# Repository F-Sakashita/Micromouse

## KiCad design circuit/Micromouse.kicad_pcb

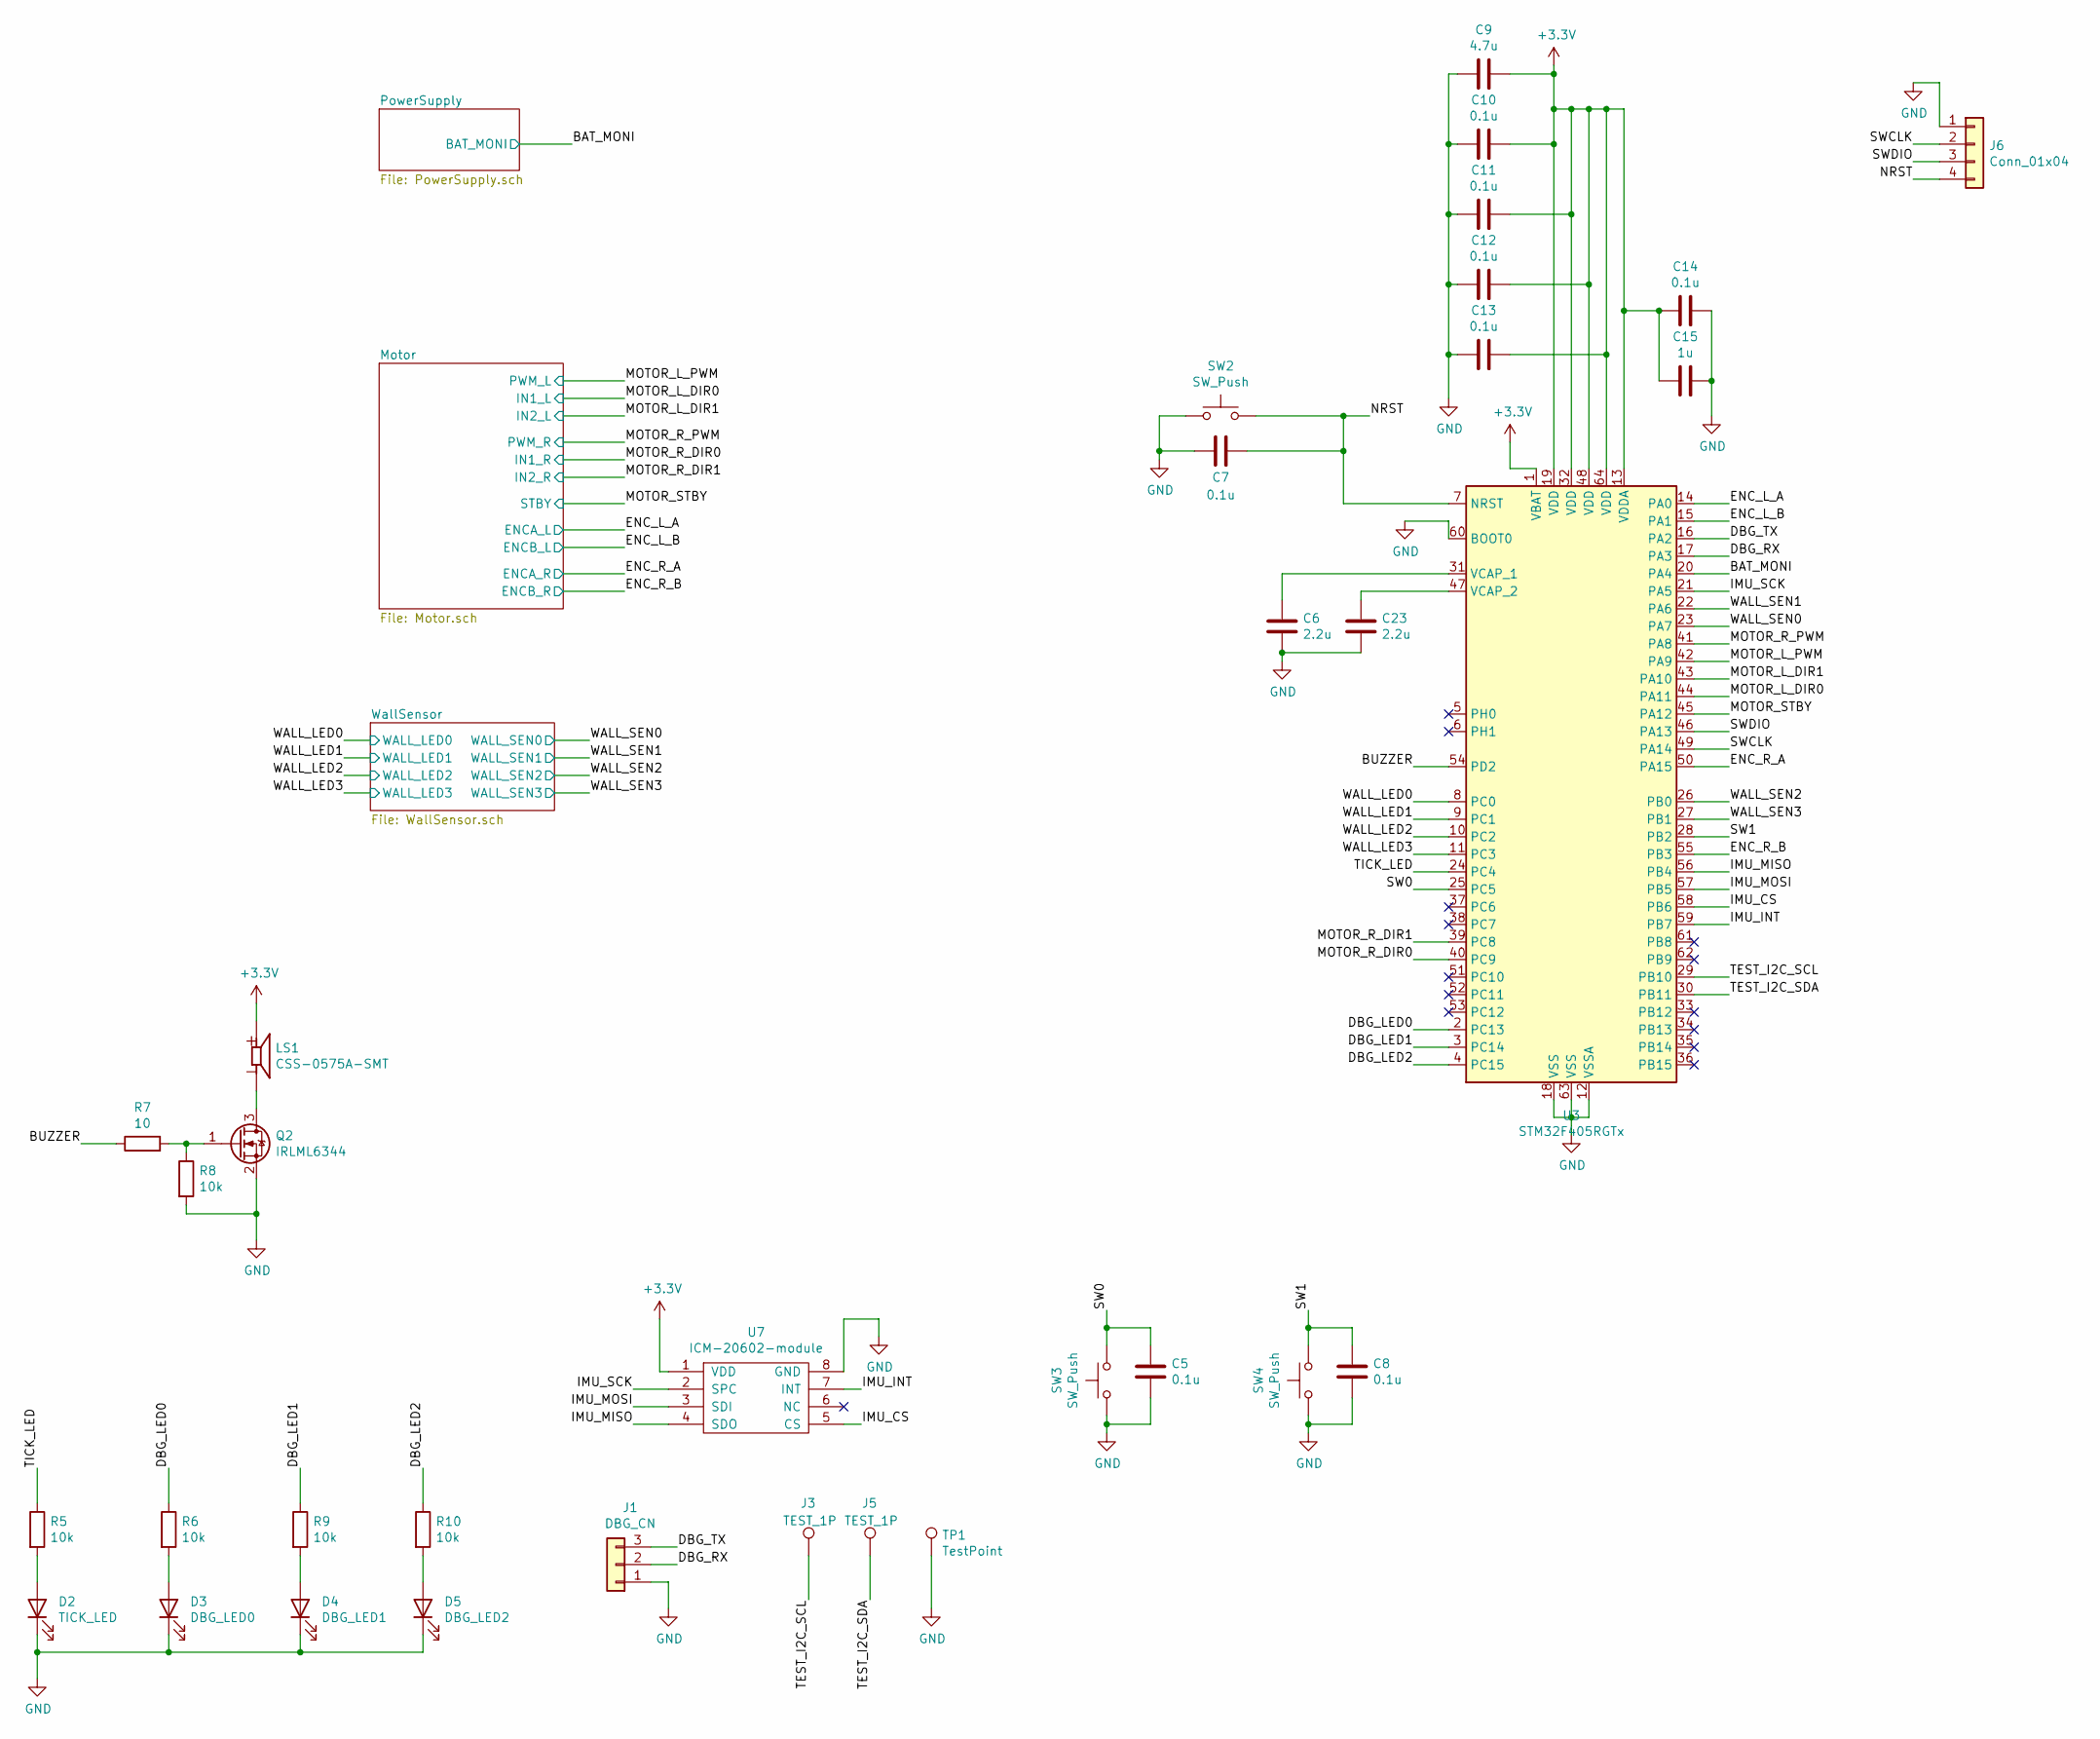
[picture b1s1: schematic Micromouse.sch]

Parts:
C5, C7, C8, C10, C11, C12, C13, C14: 0.1u; C_0603_1608Metric
C6, C23: 2.2u; C_0603_1608Metric
C9: 4.7u; C_0603_1608Metric
C15: 1u; C_0603_1608Metric
D2: TICK_LED; LED_0603_1608Metric
D3: DBG_LED0; LED_0603_1608Metric
D4: DBG_LED1; LED_0603_1608Metric
D5: DBG_LED2; LED_0603_1608Metric
J1: DBG_CN; PinSocket_1x03_P2.54mm_Vertical
J3, J5: TEST_1P; TestPoint_Pad_D1.0mm
J6: Conn_01x04; PinSocket_1x04_P2.54mm_Vertical
LS1: CSS-0575A-SMT; CUI_CSS-0575A-SMT
Q2: IRLML6344; SOT-23
R5, R6, R8, R9, R10: 10k; R_0603_1608Metric
R7: 10; R_0603_1608Metric
SW2, SW3, SW4: SW_Push; SW_TACT_ALPS_SKRPABE010
TP1: TestPoint; TestPoint_Pad_D1.0mm
U3: STM32F405RGTx; LQFP-64_10x10mm_P0.5mm
U7: ICM-20602-module; ICM-20602

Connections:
+3V3: C9.1, C10.1, C11.1, C12.1, C13.1, C14.2, C15.2, LS1.1, U3.1 (VBAT), U3.13 (VDDA), U3.19 (VDD), U3.32 (VDD), U3.48 (VDD), U3.64 (VDD), U7.1 (VDD); also elsewhere on the board
/BAT_MONI: U3.20 (PA4); also elsewhere on the board
/BUZZER: R7.1, U3.54 (PD2)
/DBG_LED0: R6.1, U3.2 (PC13)
/DBG_LED1: R9.1, U3.3 (PC14)
/DBG_LED2: R10.1, U3.4 (PC15)
/DBG_RX: J1.2, U3.17 (PA3)
/DBG_TX: J1.3, U3.16 (PA2)
/ENC_L_A: U3.14 (PA0); also elsewhere on the board
/ENC_L_B: U3.15 (PA1); also elsewhere on the board
/ENC_R_A: U3.50 (PA15); also elsewhere on the board
/ENC_R_B: U3.55 (PB3); also elsewhere on the board
/IMU_CS: U3.58 (PB6), U7.5 (CS)
/IMU_INT: U3.59 (PB7), U7.7 (INT)
/IMU_MISO: U3.56 (PB4), U7.4 (SDO)
/IMU_MOSI: U3.57 (PB5), U7.3 (SDI)
/IMU_SCK: U3.21 (PA5), U7.2 (SPC)
/MOTOR_L_DIR0: U3.44 (PA11); also elsewhere on the board
/MOTOR_L_DIR1: U3.43 (PA10); also elsewhere on the board
/MOTOR_L_PWM: U3.42 (PA9); also elsewhere on the board
/MOTOR_R_DIR0: U3.40 (PC9); also elsewhere on the board
/MOTOR_R_DIR1: U3.39 (PC8); also elsewhere on the board
/MOTOR_R_PWM: U3.41 (PA8); also elsewhere on the board
/MOTOR_STBY: U3.45 (PA12); also elsewhere on the board
/NRST: C7.1, J6.4, SW2.2, U3.7 (NRST)
/SW0: C5.1, SW3.2, U3.25 (PC5)
/SW1: C8.1, SW4.2, U3.28 (PB2)
/SWCLK: J6.2, U3.49 (PA14)
/SWDIO: J6.3, U3.46 (PA13)
/TEST_I2C_SCL: J3.1, U3.29 (PB10)
/TEST_I2C_SDA: J5.1, U3.30 (PB11)
/TICK_LED: R5.1, U3.24 (PC4)
/WALL_LED0: U3.8 (PC0); also elsewhere on the board
/WALL_LED1: U3.9 (PC1); also elsewhere on the board
/WALL_LED2: U3.10 (PC2); also elsewhere on the board
/WALL_LED3: U3.11 (PC3); also elsewhere on the board
/WALL_SEN0: U3.23 (PA7); also elsewhere on the board
/WALL_SEN1: U3.22 (PA6); also elsewhere on the board
/WALL_SEN2: U3.26 (PB0); also elsewhere on the board
/WALL_SEN3: U3.27 (PB1); also elsewhere on the board
GND: C5.2, C6.2, C7.2, C8.2, C9.2, C10.2, C11.2, C12.2, C13.2, C14.1, C15.1, C23.2, D2.1 (K), D3.1 (K), D4.1 (K), D5.1 (K), J1.1, J6.1, Q2.2 (S), R8.2, SW2.1, SW3.1, SW4.1, TP1.1, U3.12 (VSSA), U3.18 (VSS), U3.60 (BOOT0), U3.63 (VSS), U7.8 (GND); also elsewhere on the board
unnamed: C6.1, U3.31 (VCAP_1)
unnamed: C23.1, U3.47 (VCAP_2)
unnamed: D2.2 (A), R5.2
unnamed: D3.2 (A), R6.2
unnamed: D4.2 (A), R9.2
unnamed: D5.2 (A), R10.2
unnamed: LS1.2, Q2.3 (D)
unnamed: Q2.1 (G), R7.2, R8.1

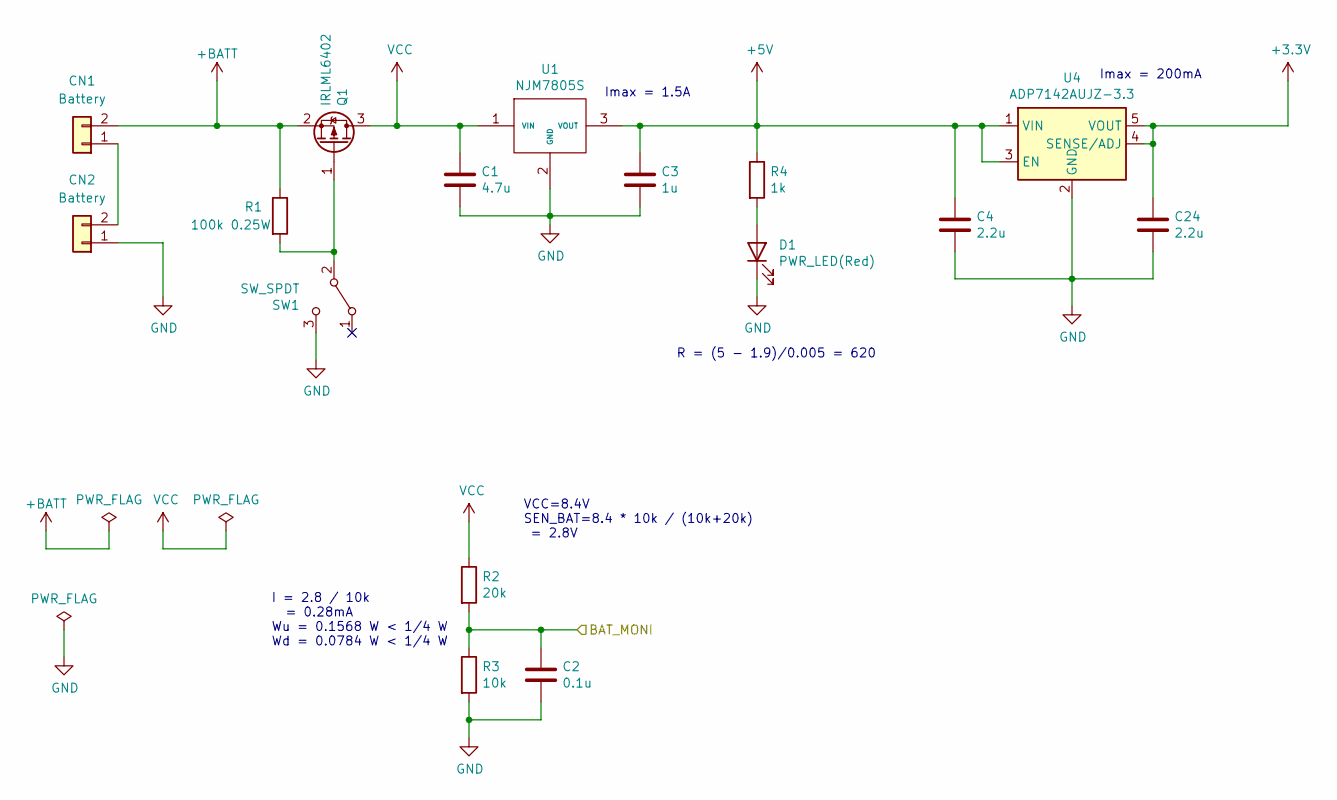
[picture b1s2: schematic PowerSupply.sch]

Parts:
C1: 4.7u; C_0805_2012Metric
C2: 0.1u; C_0603_1608Metric
C3: 1u; C_0603_1608Metric
C4, C24: 2.2u; C_0603_1608Metric
CN1, CN2: Battery; JST_PH_B2B-PH-K_1x02_P2.00mm_Vertical
D1: PWR_LED(Red); LED_0603_1608Metric
Q1: IRLML6402; SOT-23
R1: 100k 0.25W; R_0603_1608Metric
R2: 20k; R_0805_2012Metric
R3: 10k; R_0805_2012Metric
R4: 1k; R_0603_1608Metric
SW1: SW_SPDT; SW_CuK_JS202011CQN_DPDT_Straight
U1: NJM7805S; TO-252-2
U4: ADP7142AUJZ-3.3; TSOT-23-5

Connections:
+3V3: C24.1, U4.4 (SENSE/ADJ), U4.5 (VOUT); also elsewhere on the board
+5V: C3.1, C4.1, R4.1, U1.3 (VOUT), U4.1 (VIN), U4.3 (EN); also elsewhere on the board
+BATT: CN1.2, Q1.2 (S), R1.1
/BAT_MONI: C2.1, R2.2, R3.1; also elsewhere on the board
GND: C1.2, C2.2, C3.2, C4.2, C24.2, CN2.1, D1.1 (K), R3.2, SW1.3 (C), U1.2 (GND), U4.2 (GND); also elsewhere on the board
unnamed: CN1.1, CN2.2
unnamed: D1.2 (A), R4.2
unnamed 64: Q1.1 (G), R1.2, SW1.2 (B); also elsewhere on the board
VCC: C1.1, Q1.3 (D), R2.1, U1.1 (VIN); also elsewhere on the board

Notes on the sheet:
VCC=8.4V SEN_BAT=8.4 * 10k / (10k+20k) = 2.8V
Imax = 1.5A
Imax = 200mA
R = (5 - 1.9)/0.005 = 620
I = 2.8 / 10k = 0.28mA Wu = 0.1568 W < 1/4 W Wd = 0.0784 W < 1/4 W

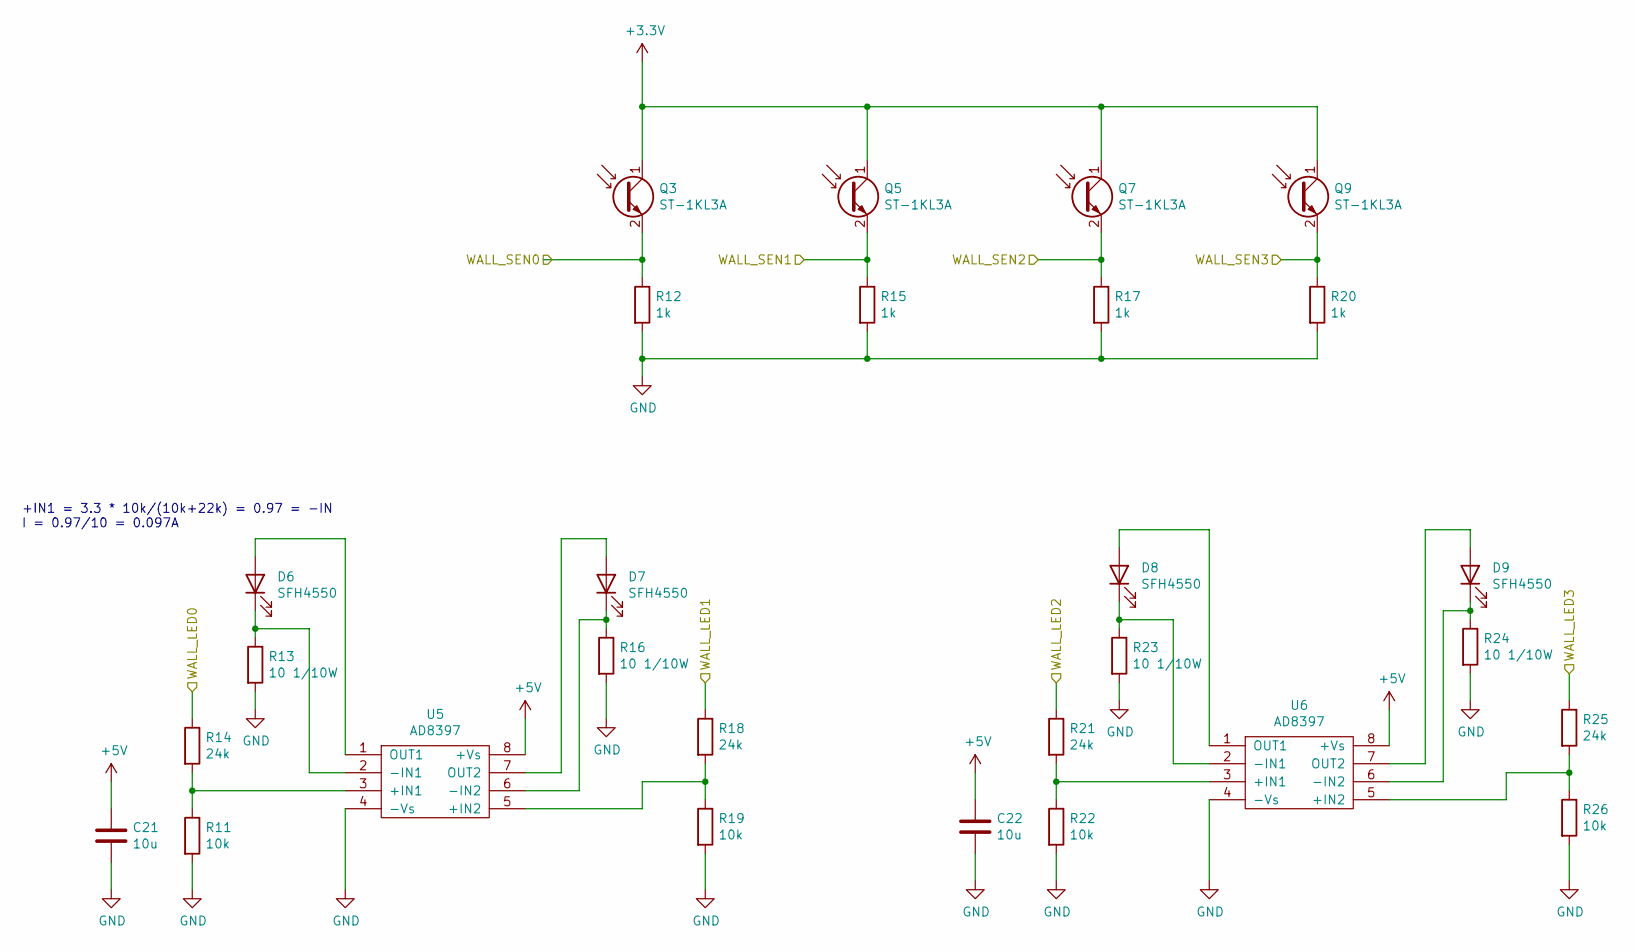
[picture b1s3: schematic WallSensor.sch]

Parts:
C21, C22: 10u; C_0603_1608Metric
D6, D7: SFH4550; LED_D5.0mm_Horizontal_O3.81mm_Z9.0mm
D8, D9: SFH4550; LED_D5.0mm_Horizontal_O3.81mm_Z9.0mm_reverse
Q3, Q5, Q7, Q9: ST-1KL3A; ST-1KL3A_ForWall
R11, R19, R22, R26: 10k; R_0603_1608Metric
R12, R15, R17, R20: 1k; R_0603_1608Metric
R13, R16, R23, R24: 10 1/10W; R_0603_1608Metric
R14, R18, R21, R25: 24k; R_0603_1608Metric
U5, U6: AD8397; SOIC-8_3.9x4.9mm_P1.27mm

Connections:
+3V3: Q3.1 (C), Q5.1 (C), Q7.1 (C), Q9.1 (C); also elsewhere on the board
+5V: C21.1, C22.1, U5.8 (+Vs), U6.8 (+Vs); also elsewhere on the board
/WALL_LED0: R14.1; also elsewhere on the board
/WALL_LED1: R18.1; also elsewhere on the board
/WALL_LED2: R21.1; also elsewhere on the board
/WALL_LED3: R25.1; also elsewhere on the board
/WALL_SEN0: Q3.2 (E), R12.1; also elsewhere on the board
/WALL_SEN1: Q5.2 (E), R15.1; also elsewhere on the board
/WALL_SEN2: Q7.2 (E), R17.1; also elsewhere on the board
/WALL_SEN3: Q9.2 (E), R20.1; also elsewhere on the board
GND: C21.2, C22.2, R11.2, R12.2, R13.2, R15.2, R16.2, R17.2, R19.2, R20.2, R22.2, R23.2, R24.2, R26.2, U5.4 (-Vs), U6.4 (-Vs); also elsewhere on the board
unnamed: D6.1 (K), R13.1, U5.2 (-IN1)
unnamed: D6.2 (A), U5.1 (OUT1)
unnamed: D7.1 (K), R16.1, U5.6 (-IN2)
unnamed: D7.2 (A), U5.7 (OUT2)
unnamed: D8.1 (K), R23.1, U6.2 (-IN1)
unnamed: D8.2 (A), U6.1 (OUT1)
unnamed: D9.1 (K), R24.1, U6.6 (-IN2)
unnamed: D9.2 (A), U6.7 (OUT2)
unnamed: R11.1, R14.2, U5.3 (+IN1)
unnamed: R18.2, R19.1, U5.5 (+IN2)
unnamed: R21.2, R22.1, U6.3 (+IN1)
unnamed: R25.2, R26.1, U6.5 (+IN2)

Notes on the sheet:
+IN1 = 3.3 * 10k/(10k+22k) = 0.97 = -IN I = 0.97/10 = 0.097A

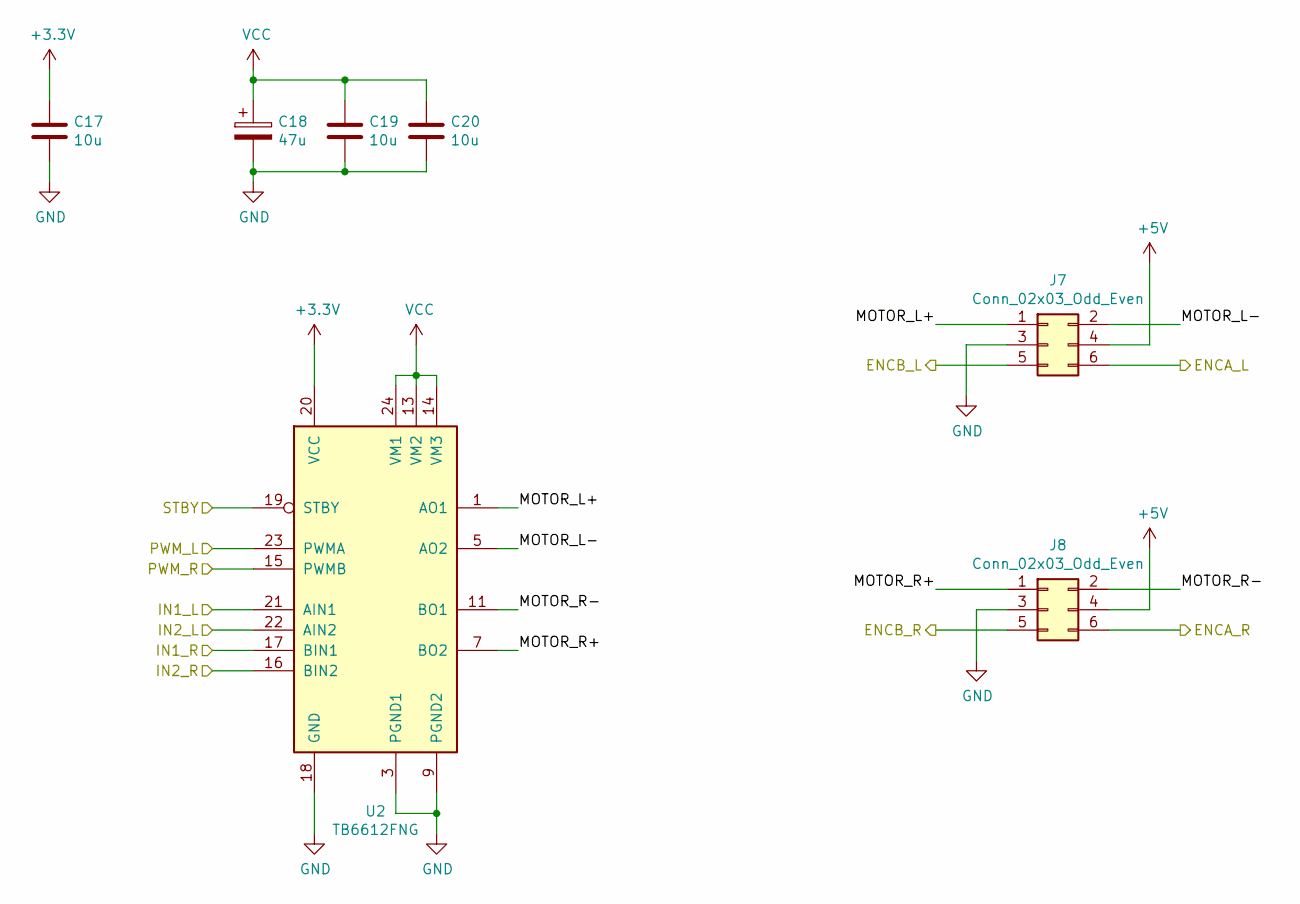
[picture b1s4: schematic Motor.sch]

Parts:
C17, C19, C20: 10u; C_0805_2012Metric
C18: 47u; CP_Elec_6.3x7.7
J7, J8: Conn_02x03_Odd_Even; IDC-Header_2x03_P2.54mm_Vertical
U2: TB6612FNG; SSOP-24_5.3x8.2mm_P0.65mm

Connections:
+3V3: C17.1, U2.20 (VCC); also elsewhere on the board
+5V: J7.4, J8.4; also elsewhere on the board
/ENC_L_A: J7.6; also elsewhere on the board
/ENC_L_B: J7.5; also elsewhere on the board
/ENC_R_A: J8.6; also elsewhere on the board
/ENC_R_B: J8.5; also elsewhere on the board
/MOTOR_L_DIR0: U2.21 (AIN1); also elsewhere on the board
/MOTOR_L_DIR1: U2.22 (AIN2); also elsewhere on the board
/MOTOR_L_PWM: U2.23 (PWMA); also elsewhere on the board
/MOTOR_R_DIR0: U2.17 (BIN1); also elsewhere on the board
/MOTOR_R_DIR1: U2.16 (BIN2); also elsewhere on the board
/MOTOR_R_PWM: U2.15 (PWMB); also elsewhere on the board
/MOTOR_STBY: U2.19 (STBY); also elsewhere on the board
/Motor/MOTOR_L+: J7.1, U2.1 (AO1), U2.2 (AO1)
/Motor/MOTOR_L-: J7.2, U2.5 (AO2), U2.6 (AO2)
/Motor/MOTOR_R+: J8.1, U2.7 (BO2), U2.8 (BO2)
/Motor/MOTOR_R-: J8.2, U2.11 (BO1), U2.12 (BO1)
GND: C17.2, C18.2, C19.2, C20.2, J7.3, J8.3, U2.3 (PGND1), U2.4 (PGND1), U2.9 (PGND2), U2.10 (PGND2), U2.18 (GND); also elsewhere on the board
VCC: C18.1, C19.1, C20.1, U2.13 (VM2), U2.14 (VM3), U2.24 (VM1); also elsewhere on the board

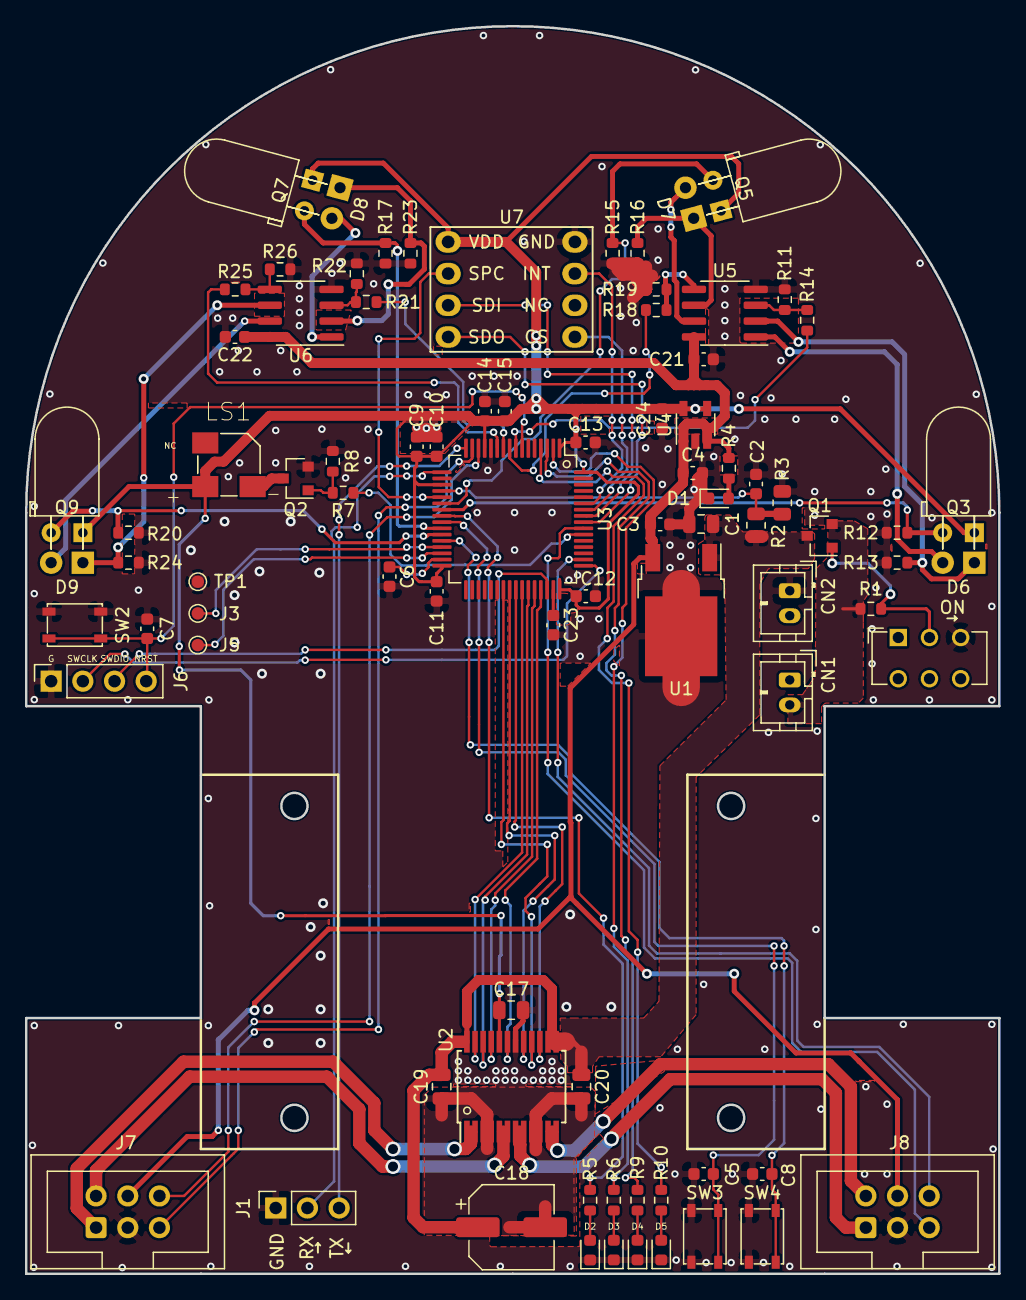
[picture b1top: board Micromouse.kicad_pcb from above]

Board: 2 copper layers, 78.0 x 100.0 mm, 85 parts (0 on the bottom side), 71 nets.

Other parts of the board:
ON: SW_SPDT; SW_CuK_JS202011CQN_DPDT_Straight

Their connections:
GND: ON.3; also elsewhere on the board
unnamed 64: ON.2; also elsewhere on the board

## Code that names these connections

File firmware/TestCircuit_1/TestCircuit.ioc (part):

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Mcu.Name=STM32F405RGTx
Mcu.Package=LQFP64
Mcu.UserName=STM32F405RGTx
PA0-WKUP.GPIOParameters=GPIO_Label
PA0-WKUP.GPIO_Label=ENC_R_A
PA0-WKUP.Signal=S_TIM5_CH1
PA1.GPIOParameters=GPIO_Label
PA1.GPIO_Label=ENC_R_B
PA1.Signal=S_TIM5_CH2
PA10.GPIOParameters=GPIO_Label
PA10.GPIO_Label=MOTOR_L_DIR1
PA10.Signal=GPIO_Output
PA11.GPIOParameters=GPIO_Label
PA11.GPIO_Label=MOTOR_L_DIR0
PA11.Signal=GPIO_Output
PA12.GPIOParameters=GPIO_Label
PA12.GPIO_Label=MOTOR_STBY
PA12.Signal=GPIO_Output
PA13.Mode=Serial_Wire
PA13.Signal=SYS_JTMS-SWDIO
PA14.Mode=Serial_Wire
PA14.Signal=SYS_JTCK-SWCLK
PA15.GPIOParameters=GPIO_Label
PA15.GPIO_Label=ENC_L_A
PA15.Signal=S_TIM2_CH1_ETR
PA2.GPIOParameters=GPIO_Label
PA2.GPIO_Label=DBG_TX
PA2.Mode=Asynchronous
PA2.Signal=USART2_TX
PA3.GPIOParameters=GPIO_Label
PA3.GPIO_Label=DBG_RX
PA3.Mode=Asynchronous
PA3.Signal=USART2_RX
PA4.GPIOParameters=GPIO_Label
PA4.GPIO_Label=BAT_MONI
PA4.Signal=ADCx_IN4
PA5.GPIOParameters=GPIO_Label
PA5.GPIO_Label=IMU_SCK
PA5.Mode=Full_Duplex_Master
PA5.Signal=SPI1_SCK
PA6.GPIOParameters=GPIO_Label
PA6.GPIO_Label=WALL_SEN0
PA6.Signal=ADCx_IN6
PA7.GPIOParameters=GPIO_Label
PA7.GPIO_Label=WALL_SEN1
PA7.Signal=ADCx_IN7
PA8.GPIOParameters=GPIO_Label
PA8.GPIO_Label=MOTOR_R_PWM
PA8.Signal=S_TIM1_CH1
PA9.GPIOParameters=GPIO_Label
PA9.GPIO_Label=MOTOR_L_PWM
PA9.Signal=S_TIM1_CH2
PB0.GPIOParameters=GPIO_Label
PB0.GPIO_Label=WALL_SEN2
PB0.Signal=ADCx_IN8
PB1.GPIOParameters=GPIO_Label
PB1.GPIO_Label=WALL_SEN3
PB1.Signal=ADCx_IN9
PB10.Mode=I2C
PB10.Signal=I2C2_SCL
PB11.Mode=I2C
PB11.Signal=I2C2_SDA
PB2.GPIOParameters=GPIO_Label
PB2.GPIO_Label=SW1
PB2.Signal=GPIO_Input
PB3.GPIOParameters=GPIO_Label
PB3.GPIO_Label=ENC_L_B
PB3.Signal=S_TIM2_CH2
PB4.GPIOParameters=GPIO_Label
PB4.GPIO_Label=IMU_MISO
PB4.Mode=Full_Duplex_Master
PB4.Signal=SPI1_MISO
PB5.GPIOParameters=GPIO_Label
PB5.GPIO_Label=IMU_MOSI
PB5.Mode=Full_Duplex_Master
PB5.Signal=SPI1_MOSI
PB6.GPIOParameters=GPIO_Label
PB6.GPIO_Label=IMU_CS
PB6.Signal=GPIO_Output
PB7.GPIOParameters=GPIO_Label
PB7.GPIO_Label=IMU_INT
PB7.Signal=GPIO_Input
PC0.GPIOParameters=GPIO_Label
PC0.GPIO_Label=WALL_LED0
PC0.Signal=GPIO_Output
PC1.GPIOParameters=GPIO_Label
PC1.GPIO_Label=WALL_LED1
PC1.Signal=GPIO_Output
PC13-ANTI_TAMP.GPIOParameters=GPIO_Label
PC13-ANTI_TAMP.GPIO_Label=DBG_LED0
PC13-ANTI_TAMP.Signal=GPIO_Output
PC14-OSC32_IN.GPIOParameters=GPIO_Label
PC14-OSC32_IN.GPIO_Label=DBG_LED1
PC14-OSC32_IN.Signal=GPIO_Output
PC15-OSC32_OUT.GPIOParameters=GPIO_Label
PC15-OSC32_OUT.GPIO_Label=DBG_LED2
PC15-OSC32_OUT.Signal=GPIO_Output
PC2.GPIOParameters=GPIO_Label
PC2.GPIO_Label=WALL_LED2
PC2.Signal=GPIO_Output
PC3.GPIOParameters=GPIO_Label
PC3.GPIO_Label=WALL_LED3
PC3.Signal=GPIO_Output
PC4.GPIOParameters=GPIO_Label
PC4.GPIO_Label=TICK_LED
PC4.Signal=GPIO_Output
PC5.GPIOParameters=GPIO_Label
PC5.GPIO_Label=SW0
PC5.Signal=GPIO_Input
PC8.GPIOParameters=GPIO_Label
PC8.GPIO_Label=MOTOR_R_DIR1
PC8.Signal=GPIO_Output
PC9.GPIOParameters=GPIO_Label
PC9.GPIO_Label=MOTOR_R_DIR0
PC9.Signal=GPIO_Output
PD2.GPIOParameters=GPIO_Label
PD2.GPIO_Label=BUZZER
PD2.Signal=GPIO_Output
RCC.HSE_VALUE=25000000
RCC.SYSCLKFreq_VALUE=168000000
RCC.SYSCLKSource=RCC_SYSCLKSOURCE_PLLCLK
board=custom

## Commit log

2020-11-01 回路設計ほぼ完了．FWのProject作成＆ピン配置決定
2020-11-02 あってぃ！
    今月中にElecrow発注したいんじゃ〜〜〜
2020-11-09 Kicad v5.1.8対応
2020-11-14 Kicadのpcbnew映らないくてキレそう
2020-11-14 スーパーエンジニアの登竜門たる文彦は当然スーパーエンジニア
    あってぃ許さない
2020-11-15 AW何も分からん
2020-11-15 ぽんぽんぺいん
2020-11-16 何となーくの部品配置
2020-11-21 配置大体完了．配線分からん
2020-11-22 1A＝1ｍｍ・・・結構大変
2020-11-22 技術メモを追加
2020-11-24 ベタ配線のやり方ちょっとわかってきた
2020-12-06 残すはGNDビアとGND分離・・・
2020-12-12 AW終わったああああああああああああああ（はず）
2020-12-27 Oppai!!!
2020-12-30 ICM-20602の値読めた〜〜
2020-12-31 大晦日に進捗出したぞオラッ！！！！！
    角速度と加速度値とれたにゃ〜〜！！
2021-01-10 Buttonクラス追加，ICM20602クラスOffset関数定義（未実装）
2021-02-14 ヨー角ヨー角ヨー角
2021-02-28 壁センサ読めた！
2021-03-26 モータ回った！
2021-04-15 数億年ぶりのコミット
2021-05-18 Delay関数のバグを直したらジャイロ動いた．
    でもまだオドメトリ計算がおかしい
2021-06-06 愛は世界を救う
    愛ゲインをあげたら幸せになった
2021-06-11 モータ制御を有効にするとジャイロが狂うバグ発生
2021-06-13 宴会芸できた
2021-06-13 速度制御タスクをリファクタリング（未デバッグ）
2021-06-13 速度制御タスクをリファクタリング（ビルドエラーなし）
2021-06-16 リファクタリング完了！！！！
2021-06-17 角度制御のデモ動作完成
